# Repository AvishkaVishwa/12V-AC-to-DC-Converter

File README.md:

# AC to DC Converter Circuit

## Overview

This project demonstrates a **230V AC to 12V DC converter** circuit that steps down the high-voltage AC input and provides a stable DC output using a step-down transformer, full-wave rectifier bridge, smoothing capacitor, and a **LM7812 voltage regulator**. The circuit is designed to convert AC mains power into a smooth 12V DC signal for low-voltage applications.
## Simulation with Proteus 

## Schematic and PCB Layout

- The circuit begins with a **230V to 12V step-down transformer** to reduce the AC voltage to a more manageable level.
- A **full-wave rectifier bridge** formed by **four diodes (D1, D2, D3, D4)** converts the 12V AC signal into a **pulsating DC voltage**.
- A **filter capacitor (C1, 1000µF)** is used to smooth the rectified DC signal, reducing any ripple.
- A **LM7812 voltage regulator** is then used to regulate the DC output to a steady 12V DC, ensuring stable voltage even with input fluctuations.
- The circuit includes an **LED indicator (D5)** with a **current-limiting resistor (R1, 2.2kΩ)** to show when the circuit is powered and functioning.
- The **AC input** is connected via the screw terminals labeled **J1** (AC In), and the **DC output** is available at the screw terminals labeled **J2** (DC Out).
- Additional resistors such as **R2 (10kΩ)** provide other functionality within the circuit, such as load balancing or voltage division.

### Upgraded Components:
- **230V to 12V Step-Down Transformer**: Converts high-voltage mains AC to 12V AC for further processing.
- **LM7812 Voltage Regulator**: Ensures the output is a stable 12V DC, regardless of fluctuations in the AC input.

### PCB Design

- The **PCB layout** reflects the placement of the transformer, diodes, capacitors, and the voltage regulator.
- **Through-hole components** are used to simplify assembly and soldering.
- The copper traces connecting the components are designed to handle the appropriate current, ensuring minimal resistance and optimal performance.
- **Ground (GND)** and **positive voltage output (+VE)** traces are clearly marked on the PCB to assist in proper wiring.

## Operation

1. The **230V AC input** is connected to the **step-down transformer**, which reduces it to 12V AC.
2. The **12V AC** is fed into the **full-wave rectifier bridge**, converting it to a pulsating DC signal.
3. A **filter capacitor** smooths the DC signal to reduce any ripple.
4. The **LM7812 voltage regulator** further stabilizes the output to provide a steady **12V DC**.
5. An **LED** indicates the power status, lighting up when the circuit is operating correctly.

## Features

- **Step-Down Transformer**: Safely reduces 230V AC mains to 12V AC.
- **Full-Wave Rectifier**: Converts the 12V AC signal into DC using four diodes.
- **Voltage Regulation**: The LM7812 ensures a stable 12V DC output even if the input fluctuates.
- **Ripple Reduction**: The 1000µF capacitor smooths the DC signal by reducing ripple.
- **LED Power Indicator**: Provides a visual confirmation that the circuit is operational and receiving power.
- **PCB Layout**: Includes screw terminals for easy connection of AC input and DC output, making assembly and usage straightforward.

## How to Use

1. **Connect the AC input** (230V AC) to the terminals labeled **AC In**.
2. **Connect the DC load** (such as a low-voltage device) to the terminals labeled **DC Out**.
3. Once powered, the **LED** will light up to indicate the circuit is functioning correctly.
4. Measure the output voltage at the **DC Out** terminals, which should be a stable **12V DC**.
5. Use the system to power your 12V DC devices efficiently.

## Components

- **Step-Down Transformer**: 230V to 12V AC
- **Diodes**: 4 x 1N4007 (for rectification) or Bridge Rectifier Module
- **Capacitor**: 1 x 1000µF (for smoothing)
- **Voltage Regulator**: LM7812 (for voltage regulation)
- **Resistors**:
  - R1: 2.2kΩ (current-limiting resistor for LED)
  - R2: 10kΩ (for additional functionality)
- **LED**: Power status indicator
- **Screw Terminals**: 2 x Screw_Terminal_01x02 (for AC input and DC output)

## Upgraded Features

- **Transformer Addition**: The addition of the **230V to 12V step-down transformer** ensures that the circuit can be connected directly to mains power, making it suitable for real-world applications.
- **Voltage Regulation**: The **LM7812** voltage regulator ensures the output voltage is consistently 12V DC, which is crucial for sensitive electronics that require stable power.

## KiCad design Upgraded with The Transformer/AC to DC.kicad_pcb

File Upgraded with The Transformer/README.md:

# AC to DC Converter Circuit

## Overview

This project demonstrates a simple **AC to DC converter** circuit that converts an AC voltage input into a smooth DC voltage output. The circuit is based on a full-wave rectifier bridge, filtering components, and an LED indicator for power status.

## Schematic and PCB Layout

- The circuit uses **four diodes (D1, D2, D3, D4)** to form a **full-wave rectifier bridge**, which converts the incoming **AC (Alternating Current)** signal into a **DC (Direct Current)** output.
- A **capacitor (C1, 1000µF)** acts as a **filter capacitor**, smoothing out the rectified DC signal by reducing any remaining ripple.
- The circuit includes an **LED (D5)**, accompanied by a **current-limiting resistor (R1, 2.2kΩ)**, which indicates when the circuit is powered.
- A second resistor **(R2, 10kΩ)** is included for additional functionality, potentially for voltage division or a secondary operation within the circuit.
- The **AC input** is connected via the screw terminals labeled **J1** on the left side of the board, and the **DC output** is available at the screw terminals labeled **J2** on the right side.

### PCB Design

- The **PCB layout** shows the copper traces that connect the diodes, capacitor, resistors, and LED components.
- The design uses **through-hole components** for easy assembly.
- The traces for **ground (GND)** and **positive voltage output (+VE)** are clearly marked to ensure proper wiring during assembly.

</br>

## Operation

- The circuit accepts an **AC voltage input** and converts it to **DC voltage** through the full-wave rectifier bridge (formed by the four diodes).
- The **filter capacitor (C1)** smooths the rectified output to reduce ripple and provide a cleaner DC signal.
- The **LED** serves as a **power indicator**, lighting up when the circuit is operational.

## Features

- **Full-Wave Rectifier**: Converts AC to DC with the help of four diodes.
- **Ripple Reduction**: The 1000µF capacitor reduces ripple, providing a stable DC output.
- **LED Power Indicator**: Provides a visual confirmation that the circuit is receiving power and functioning properly.

## How to Use

1. Connect the AC input source to the terminals labeled **AC in**.
2. Attach your DC-powered device to the terminals labeled **DC out**.
3. When power is supplied, the **LED** will light up, indicating the circuit is functioning.
4. The output voltage can be measured at the **DC out** terminals to verify the conversion from AC to DC.

## Components

- **Diodes**: 4 x 1N4007
- **Capacitor**: 1 x 1000µF
- **Resistors**:
  - R1: 2.2kΩ (current-limiting resistor for LED)
  - R2: 10kΩ
- **LED**: Power indicator
- **Screw Terminals**: 2 x Screw_Terminal_01x02 (for AC input and DC output)

## License

This project is licensed under the MIT License - see the [LICENSE](LICENSE) file for details.

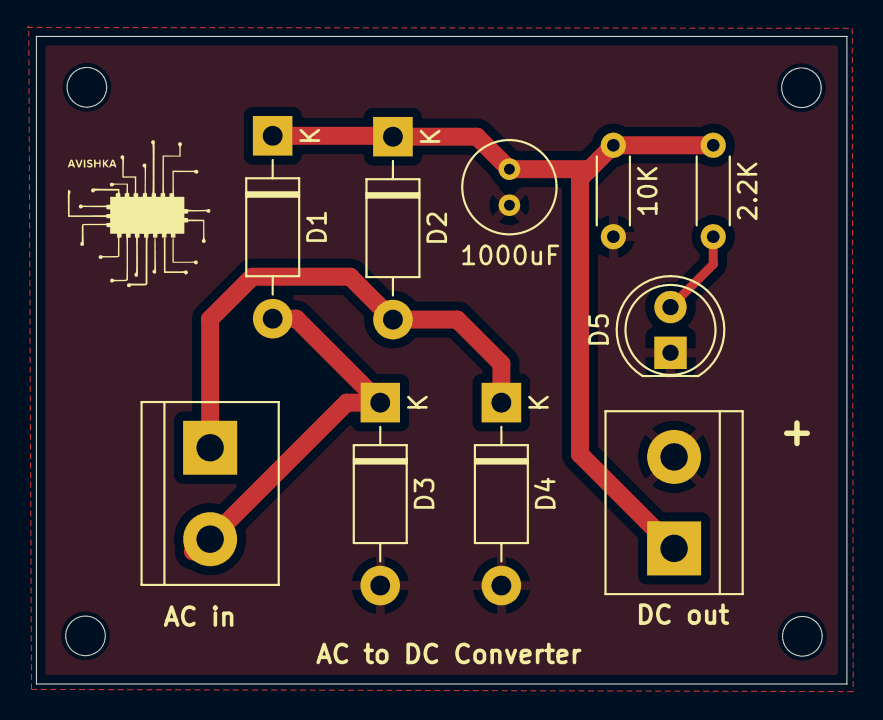
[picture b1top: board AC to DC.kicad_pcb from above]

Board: 2 copper layers, 45.0 x 36.0 mm, 14 parts (0 on the bottom side), 5 nets.

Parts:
2.2K: 2.2k; R_Axial_DIN0204_L3.6mm_D1.6mm_P5.08mm_Horizontal
10K: 10k; R_Axial_DIN0204_L3.6mm_D1.6mm_P5.08mm_Horizontal
1000uF: 1000uF; C_Radial_D5.0mm_H7.0mm_P2.00mm
D1, D2, D3, D4: 1N4007; D_DO-41_SOD81_P10.16mm_Horizontal
D5: LED; LED_D5.0mm
H1, H2, H3, H4: MountingHole; MountingHole_2.2mm_M2
Input: Screw_Terminal_01x02; TerminalBlock_bornier-2_P5.08mm
Output: Screw_Terminal_01x02; TerminalBlock_bornier-2_P5.08mm

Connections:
/+VE: 2.2K.1, 10K.1, 1000uF.1, D1.1 (K), D2.1 (K), Output.1
GND: 10K.2, 1000uF.2, D3.2 (A), D4.2 (A), D5.1 (K), Output.2
unnamed: D1.2 (A), D3.1 (K), Input.2
unnamed: D2.2 (A), D4.1 (K), Input.1
unnamed: 2.2K.2, D5.2 (A)

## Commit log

2024-10-14 main
